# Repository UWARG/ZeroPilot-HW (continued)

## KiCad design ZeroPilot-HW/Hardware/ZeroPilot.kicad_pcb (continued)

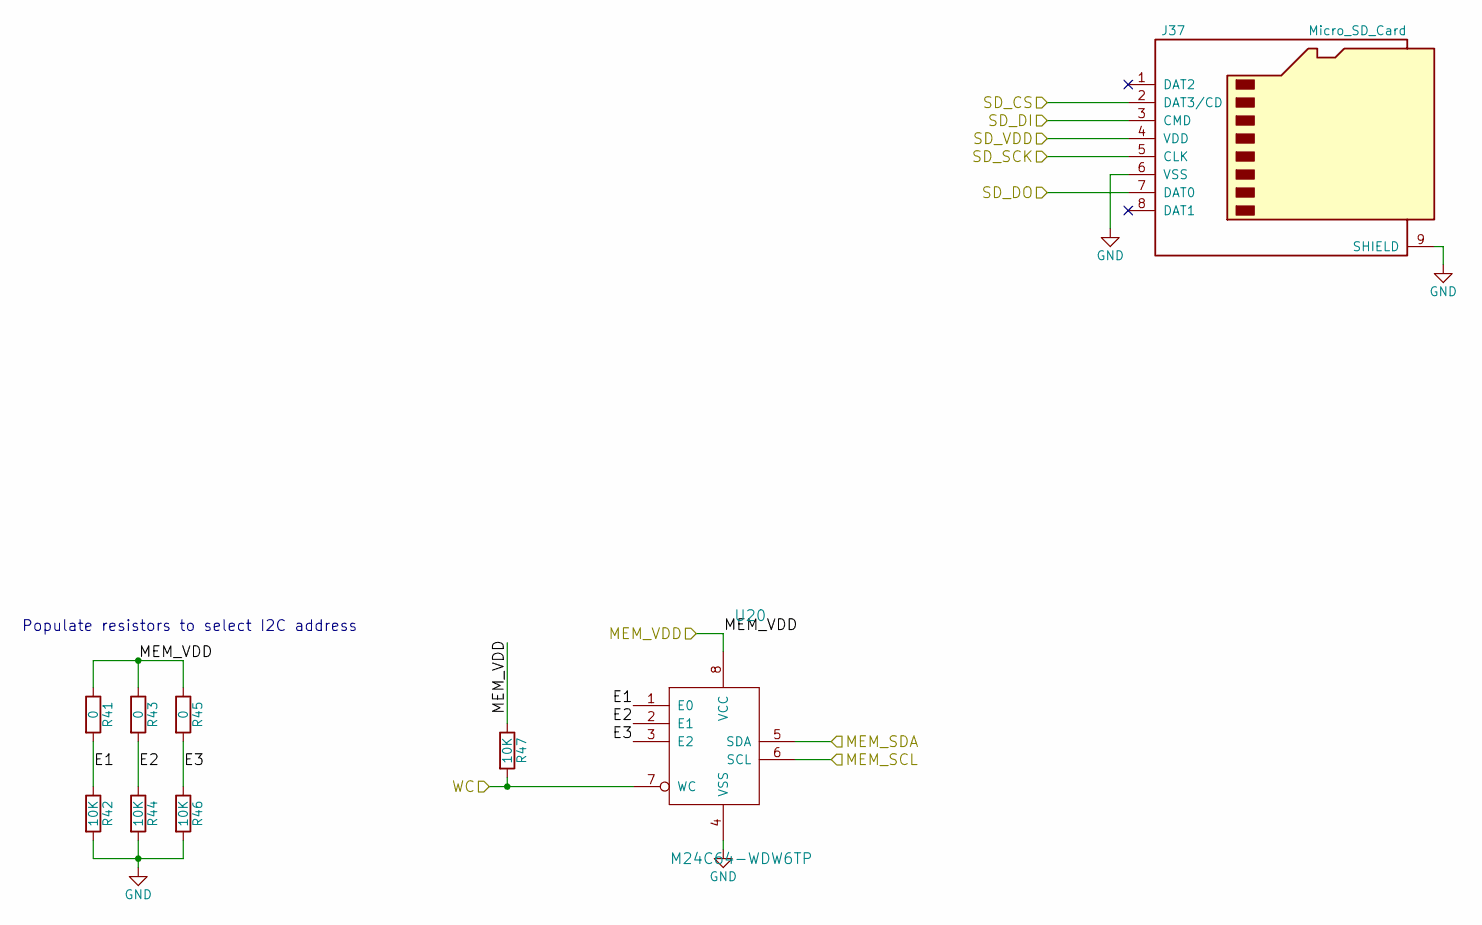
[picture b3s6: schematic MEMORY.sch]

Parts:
J37: Micro_SD_Card; micro_sd; part_num MEMM-002
R41, R43, R45: 0; R_0603_HandSoldering; part_num RESS-001
R42, R44, R46, R47: 10K; R_0603_HandSoldering; part_num RESS-005
U20: M24C64-WDW6TP; TSSOP-8_4.4x3mm_Pitch0.65mm; part_num MEMM-001

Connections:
/3V3: J37.4 (VDD), R41.1, R43.1, R45.1, R47.1, U20.8 (VCC); also elsewhere on the board
/MEMORY/E1: R41.2, R42.1, U20.1 (E0)
/MEMORY/E2: R43.2, R44.1, U20.2 (E1)
/MEMORY/E3: R45.2, R46.1, U20.3 (E2)
/MEM_WC: R47.2, U20.7 (WC); also elsewhere on the board
/MISO5: J37.7 (DAT0); also elsewhere on the board
/MOSI5: J37.3 (CMD); also elsewhere on the board
/NSS5: J37.2 (DAT3/CD); also elsewhere on the board
/SCK5: J37.5 (CLK); also elsewhere on the board
/SCL1: U20.6 (SCL); also elsewhere on the board
/SDA1: U20.5 (SDA); also elsewhere on the board
GND: J37.6 (VSS), J37.9 (SHIELD), R42.2, R44.2, R46.2, U20.4 (VSS); also elsewhere on the board

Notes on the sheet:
Populate resistors to select I2C address

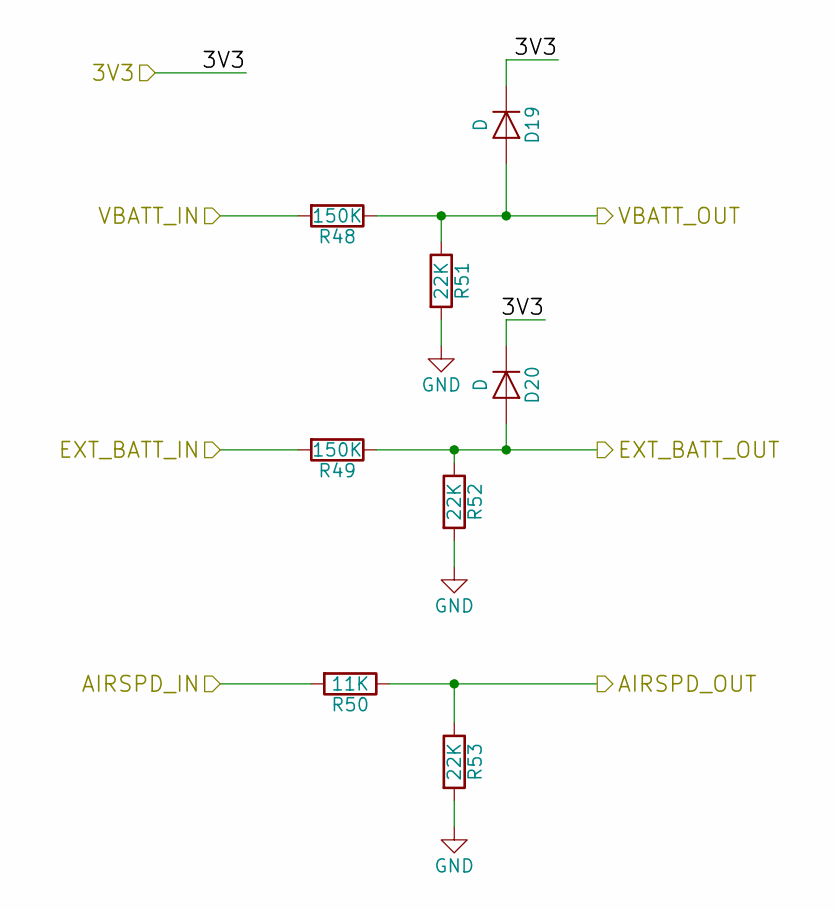
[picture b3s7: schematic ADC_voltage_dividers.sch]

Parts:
D19, D20: D; D_SOD-523; part_num DIOD-004
R48, R49: 150K; R_0603_HandSoldering; part_num RESS-007
R50: 11K; R_0603_HandSoldering; part_num RESS-004
R51, R52, R53: 22K; R_0603_HandSoldering; part_num RESS-002

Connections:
/3V3: D19.1 (K), D20.1 (K); also elsewhere on the board
/AIRSPD_ADC: R50.1, R53.1; also elsewhere on the board
/AIR_SPD: R50.2; also elsewhere on the board
/EXT_BATT: R49.2; also elsewhere on the board
/EXT_BATT_ADC: D20.2 (A), R49.1, R52.1; also elsewhere on the board
/VBATT: R48.2; also elsewhere on the board
/VBATT_ADC: D19.2 (A), R48.1, R51.1; also elsewhere on the board
GND: R51.2, R52.2, R53.2; also elsewhere on the board

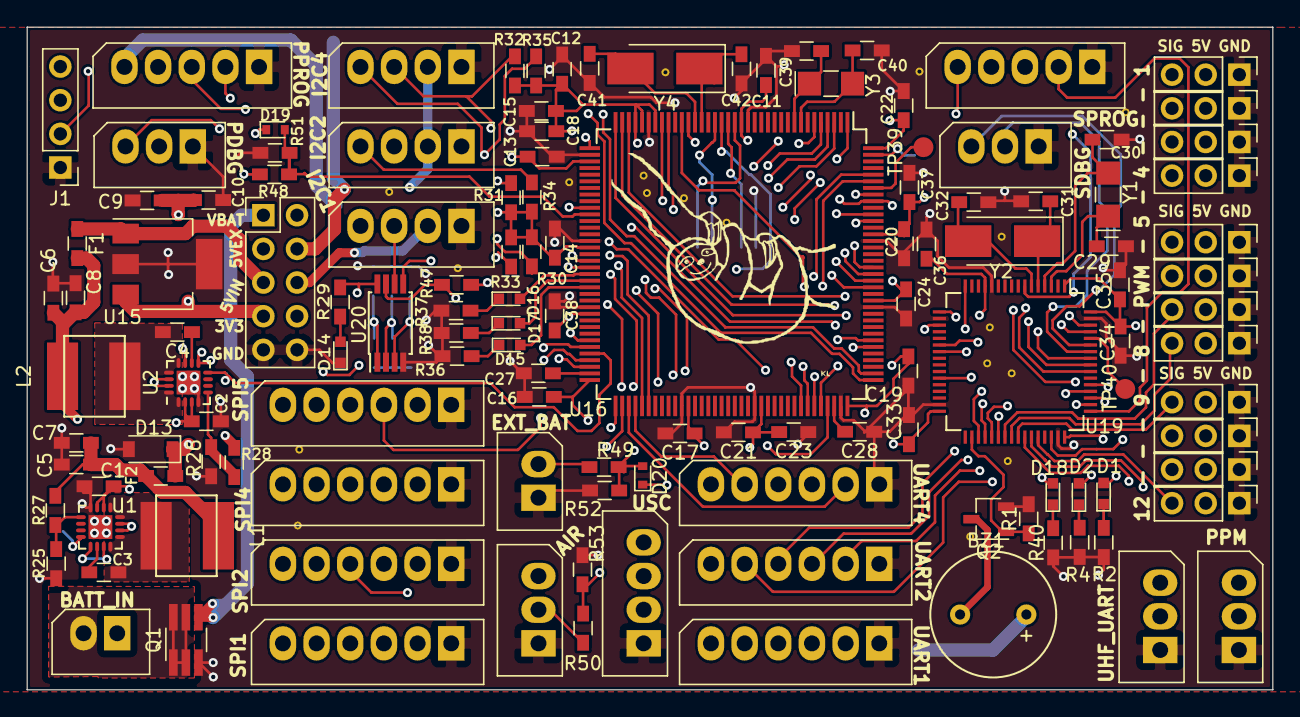
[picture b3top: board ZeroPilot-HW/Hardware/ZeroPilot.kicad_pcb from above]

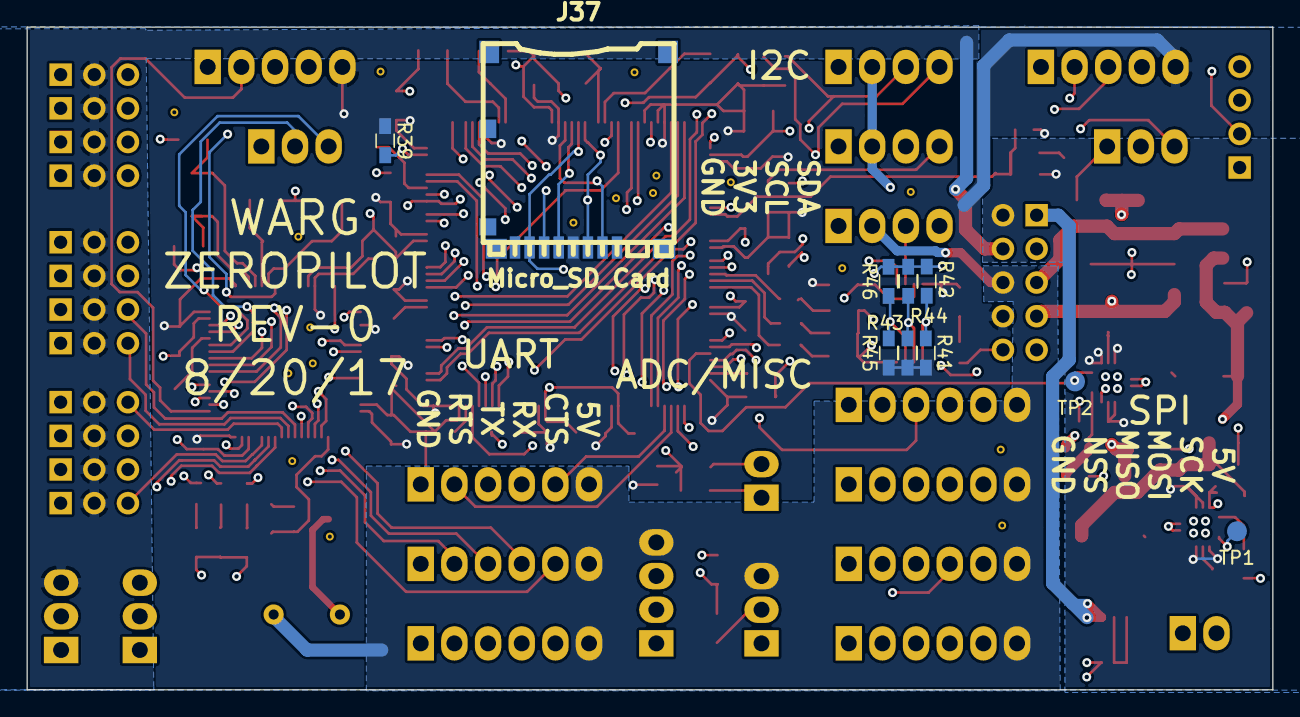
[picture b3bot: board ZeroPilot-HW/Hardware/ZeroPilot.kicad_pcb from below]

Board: 4 copper layers, 94.0 x 50.0 mm, 138 parts (10 on the bottom side), 121 nets.

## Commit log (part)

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2017-05-13 Initial commit setting up the project
2017-05-14 Added PWM switch stuff
2017-05-14 Renamed project
2017-05-14 Added gitignore, started adding STM
2017-05-14 ALL THE POWER
2017-05-14 Added library
2017-05-14 Added library submodule
2017-05-14 Added gitignore, finished F7 chip
2017-05-14 Added F7 chip
2017-05-14 Added F0 chip
2017-05-14 Connected Relay together
2017-05-16 Added F7 circuitry
2017-05-16 Added extra IOs
2017-05-17 Added headers
2017-05-18 Reconfiguring pinout round 2
2017-05-18 Added a pdf for those too lazy to setup kicad
2017-05-18 branch to make PR for review
    I should have made a separate branch for the development and then merged
    it, but its too late now.
2017-05-19 Added component library
2017-05-19 Added short component
2017-05-19 Added a lot of debug
2017-05-22 Fixed some BOM stuff
    fixed BOM for non RLC components
2017-05-22 Fixed BOM, added SD card
2017-05-24 Added ressistor footprint
2017-05-25 PCB?!
    Added initial PCB file with ratsnest. footprint library still needs to
    be setup.
2017-05-26 Added BOM manager
2017-05-27 Redid all of my work
    Redid all the digikey #s for the components.
2017-05-28 Fixed serge suggestions
2017-05-28 Updated diode
2017-05-29 Quickly commit before my computer restarts
2017-05-29 vague pcb placements
    still needs the sd card footprint
2017-05-29 routed PWM and SEL bus
2017-05-29 finished safety controller routing
2017-05-31 placed headers in roughly correct spot
2017-06-01 adc routing, made board smaller
2017-06-01 imported micro sd footprint
2017-06-01 imported micro sd footprint
    Import conn library from the interwebs to get the micro sd card
    footprint.
2017-06-04 finished signal routing
2017-06-04 finished all routing except gnd
2017-06-04 A fully routed (shitty) board!
2017-06-06 This power is HUGE
    Made some big traces and pours for power. Need to do some ground layer
    stiching to fix the ground plane still
2017-06-06 changed sd card part
2017-06-06 Holy Power
    Added a ton of stitching to the power section. Never enough vias.
2017-06-06 Holy Pilot
    Added stiching around STMF7 chip
2017-06-07 Is too much stitching a thing?
    Its concerning when you start to become worried about the structural
    integrity of the board because of too many vias... oh well, I think its
    fine
2017-06-17 June 2017 Inventory
    Completed ARMPilot component inventory
2017-06-18 added component descriptions
2017-06-18 ZeroPilot Component Inventory Update
    Re-inventoried parts to reflect identical components with different
    Digikey part numbers. Also compiled list of similar components at end of
    inventory.
2017-06-18 Minor Inventory Changes
    Confirmed we did not have any 100k 1% resistors. Removed apostrophe
    characters so csv is formatted properly.
2017-06-18 Removed comma in row 18
2017-06-24 added speaker
2017-07-30 Restarted work
    Removed OC and SEL busses. Still need to add clocks.
2017-08-12 Placement and preminiary routing
2017-08-12 power placement and experimental routing
2017-08-12 Routed decoupling caps and power supply
2017-08-12 Power plane flooding
2017-08-12 Fully placed board
    Placed board, also fixed I2C pullup bug
2017-08-13 routed safety controller
2017-08-13 routed UART, started SPI
2017-08-13 Updated schematic to make routing easier
2017-08-13 Routed some I2C
2017-08-15 Board fully routed
2017-08-15 Copper balancing
    Copper balanced the inner layers
2017-08-15 Power circuitry pouring
2017-08-17 Cleaned up silkscreen
2017-08-20 Bottom silk screen and improved stiching
2017-08-21 Updated pdfs
2017-08-22 Added new F0 chip
2017-08-22 Added speaker buffer
2017-08-22 Added sloth and buzzer stuff
2017-08-22 Rev0 Final
2017-08-23 Cleaned up component library
2017-08-25 Removed KiCad BOM Wizard
    I added a BOM script to WARG-KiCad repo so this is no longer needed
2017-09-09 Library Update & Part Removal
    Added AP3211KTR IC to WARG library & removed linear voltage regulator
2017-09-09 Updated Schematic
    Added the switching power regulator to the schematic along with it's components.
2017-09-09 Updated Footprint Locations
    Changed footprint locations to be local to my machine & enumerated the newly added componenets.
2017-09-10 Added 2nd Layer Traces and Vias
2017-09-10 Actually connected the parts
2017-09-21 Updated BOM Generator
    Added part references and whether or not a part is no_load. Fixed bug with part numbers. Changed dependency from python elementTree to lxml because elemenTree cannot move up/down parent/child element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
2017-09-21 Added new features
    Added ability for new fields to be added in KiCad without any need for refactoring the script. Added warning message for parts that are in the netlist, but missing from the component library.
2017-09-22 Fixed bugs
    Changed the variable named 'p', changed missing part error from looking for distributor numbers to looking for part_name entries in the component library, removed debug lines, changed path for compon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
2017-09-22 Changed file paths
    Changed from using text-only file path to using the os library for opening the component library.
2017-09-22 Removed pip library
2017-09-24 Open BOM on generation
2017-10-26 Added new buck regulator for bootcamp
2017-11-22 Replaced inductor and minor tweaks
2018-01-25 please work god
2018-01-25 I think this is everything
2018-01-30 DId the bootcamp. Selected mEZD71201A buck regulator
2018-02-08 Switched out LDO for TI DC-DC Converter
2018-02-08 Replaced LDO
2018-03-28 Re-routed 3V3 input to after jumper
2018-03-28 Update WARG-kicad, remove Stephen-specific paths
2018-03-28 PCB update
2018-03-28 Fix PPM and Airspeed connector pinouts
2018-03-29 Add shield ground to micro SD card footprint
2018-03-29 Fix spelling
2018-05-08 Replaced 3.3V buck regulator
    Replaced the old 3.3V linear regulator with a new buck regulator in the Power schematic and on the ZeroPilot PCB.
2018-05-22 Fixed 3.3V Reg Inductor
    Replaced the 3.3V 47uH inductor with a properly spec'd one.
2018-05-22 Fixed Trace Width Issue on 3.3V Regulator
    Fixed opposite usage of trace width and vias for 3V3_JMP and output pin for 3.3V regulator.
2018-05-24 Changed SPI pinout
2018-05-30 Added IMU and Altimeter schematics and footprints
2018-05-31 Fixed altimeter schematic
2018-05-31 Removed duplicate folder
2018-05-31 Added part nums to IMU and altimeter, updated csv file
2018-06-04 Added footprint values and part nums to capacitors
    Also added part nums on the sheet to the sensors, however they already exist in the footprint editor
2018-06-05 Added error checking
2018-06-05 Added test points, updated footprint values, fixed J1, replaced connectors
2018-06-05 Fixed merge conflicts
2018-06-07 Updated fp-lib-table
2018-06-07 Updated footprint field for capacitors in sensors sheet
2018-06-07 Fixed part_num field in PWM sheet
2018-06-07 Added IMU and Altimeter schematics and footprints (#15)
    * Added IMU and Altimeter schematics and footprints
    * IMU and altimeter schematics and footprints
    * Updated csv file and WARG.lib
    * Updated csv
    * Updated years on inventory date for new sensors
    * Update README.md
2018-06-07 Added USB Interface Sheet
    Added hierarchically, under ZeroPilot.sch.
2018-06-08 Almost Done USB Interface
2018-06-17 Finalized USB Interface
    Added SWD line resistors
2018-06-18 Fixed Missing Bits
    Fixed missing crystal part_num and added hierarchical pin for VBUS.
2018-06-19 Added load switch circuit - defaults to batery power when available
2018-06-19 Deleted Zeropilot-cache library
2018-06-20 Added capacitors, inductors, inverter and load switches
2018-06-20 Updated Part Number
2018-06-22 Added Test Points for USB Interface
    Added JTAG and UART test points for the FT4232H
2018-06-22 Bug Fixes
    Fixed hierarchical pin naming typos
2018-06-23 Updated part numbers
2018-06-23 fixed sensor sheet from merge
2018-06-24 Updated component_library.csv to match Alex's, fixed footprint library
2018-06-24 Fixed Sensors.sch sheeet
    Windows hates the world and decides files don't need to be case sensitive, but git does.
2018-06-24 Scholvat patch 1 (#12)
    * Fixed Sensors.sch sheeet
    Windows hates the world and decides files don't need to be case sensitive, but git does.
    * Delete sensors.sch
2018-06-26 Fixed HEADERS.sch file
2018-06-26 Fixed merge issues
2018-06-29 Starting from scratch
2018-07-03 Updated Resistors
    Changed 1K resistors on DBUS1 lines to 220R resistors and 100R resistors on DBUS2 lines to 0R resistors, on the FT4232H.
2018-07-05 Deleted Old TPs
2018-07-10 Fixed one more bug
    Fixed overwritten part num
2018-07-10 Removed unused connectors, started placements of components on new board
2018-07-11 Rough board placements
2018-07-16 Capacitors where they should be on the pcb, usb interface moved
2018-07-16 Revert "Add files via upload"
    This reverts commit 5604160992b0e2f63895336bcd07dee2b13465c5.
2018-07-17 Revert "Add files via upload"
    This reverts commit da10b5fdad91ea60d4fa12b31fc0ca8e44e0347f.
2018-07-17 Updated REV1 branch with changes from USB Interface Revision
2018-07-18 Removed J20, added smaller inductor, updated placements
2018-07-23 Placements and routing
2018-07-24 Updated schematic
    -Changed diode to 0603 diodes
    -Changed SD card to proper pinout
    -Fixed SPI1 conflict
    -Renamed some power nets
    -Fixed naming error in IMU NSS
2018-07-31 Updated pcb
2018-08-22 Added copper ground pours to Layer 1 and 4
2018-09-26 Removed back layer SCL1 trace from under U13
2018-10-01 Moved U8 output capacitors closer to output pin, fixed disconnected test point
2018-10-12 Fixes to INDU-003 and DIOD-005
    Changed DIOD-005 (D1 and D2) to D_SMA instead of D_SMA_Handsoldering. Created new INDU-003 footprint as per datasheet. Ensured proper routing on layout.
2018-10-31 Updated stackup text
2018-11-15 Changed "Signals" in stackup text to "3.3V"
2019-04-12 Added RSSI, datasheets, INDU-004
    Added RSSI input to PPM connector. Added datasheets for most of the components. The filter inductors for the FTDI were labeled as INDU-002, which is a 15uH smps inductor.
2019-04-15 Fixed safety schematic references with new warg lib
2019-04-15 Fixed Safety UART1
    UART 1 pins were flipped on safety controller.
2019-04-15 Bug fixes, added Isense, changed conn to JST-GH
    Added boot0 pull-down resistors. Changed ext_batt to current sense line. Changed spox conn to JST-GH, this will dramatically reduce the required size of the board.
2019-04-15 Ported to kicad5
2019-04-17 Removed F0 SPI, gave Baro its own I2C line, changed IMU to SPI1
2019-04-17 Fixed IMU and Baro symbols
2019-04-17 Generated netlist and board outline
2019-05-14 Initial Routing of Zeropilot Rev1
    This is the initial routing of the board. It needs to be cleaned up slightly, but library references are screwed up so they will be fixed first.
2019-05-17 Update of bootcamp
    Kicad 5.1 and Zeropilot R1
2019-05-17 HW Bootcamp for Zeropilot R1
    Changed the board to R1.
2019-05-17 Removed unused sch sheets.
2019-05-19 New chip, finishing touches
    Upgraded the safety chip to F091. SPI6 from main to safety. Cleaned up silkscreen. Added front and back Cu fill.
2019-05-20 Library Issues
    They are finally not screwed up.
2019-05-30 Silkscreen and Gerbers
    Finalized silkscreen, generated gerbers, moved current sense input.
2019-06-03 Bug fixes
2019-06-08 Fixes
2019-07-06 Dual Power Supply
    Added a fail-over power supply that will connect to a secondary battery.
2019-08-03 Finalized Battery Switch
2020-11-16 IMU Fix
    Small interface board to fix footprint mismatch.
2020-11-16 Fixed design rules
    Design rules were not auto applying.
2021-02-03 bootcamp
2021-04-02 Revert "bootcamp"
    This reverts commit e17f23a9567473d5c63a4d79c7567bac12ecac0d.
